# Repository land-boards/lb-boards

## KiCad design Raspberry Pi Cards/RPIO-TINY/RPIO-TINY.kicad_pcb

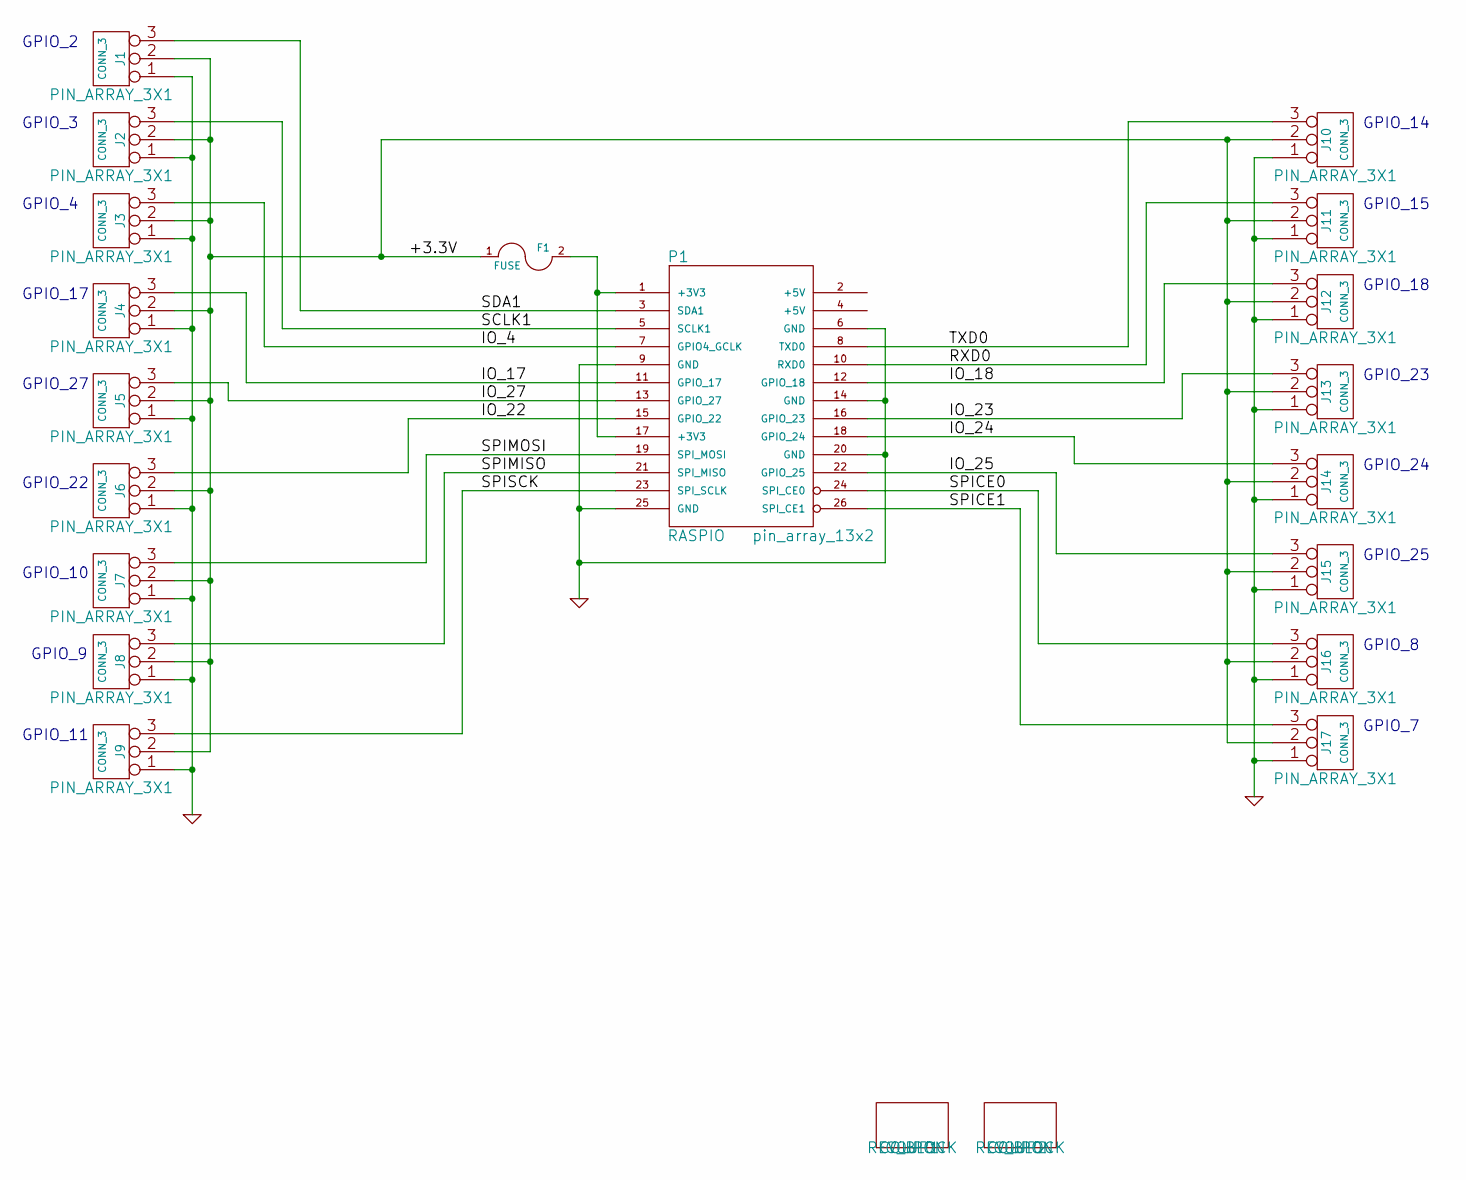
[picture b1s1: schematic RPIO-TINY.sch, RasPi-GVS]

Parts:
COUP1, COUP2: COUPON; REV_BLOCK
F1: FUSE
J1, J2, J3, J4, J5, J6, J7, J8, J9, J10, J11, J12, J13, J14, J15, J16, J17: CONN_3; PIN_ARRAY_3X1
P1: RASPIO; pin_array_13x2

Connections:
/+3.3V: F1.1, J1.2 (PM), J2.2 (PM), J3.2 (PM), J4.2 (PM), J5.2 (PM), J6.2 (PM), J7.2 (PM), J8.2 (PM), J9.2 (PM), J10.2 (PM), J11.2 (PM), J12.2 (PM), J13.2 (PM), J14.2 (PM), J15.2 (PM), J16.2 (PM), J17.2 (PM)
/IO_4: J3.3, P1.7 (GPIO4_GCLK)
/IO_17: J4.3, P1.11 (GPIO_17)
/IO_18: J12.3, P1.12 (GPIO_18)
/IO_22: J6.3, P1.15 (GPIO_22)
/IO_23: J13.3, P1.16 (GPIO_23)
/IO_24: J14.3, P1.18 (GPIO_24)
/IO_25: J15.3, P1.22 (GPIO_25)
/IO_27: J5.3, P1.13 (GPIO_27)
/RXD0: J11.3, P1.10 (RXD0)
/SCLK1: J2.3, P1.5 (SCLK1)
/SDA1: J1.3, P1.3 (SDA1)
/SPICE0: J16.3, P1.24 (SPI_CE0)
/SPICE1: J17.3, P1.26 (SPI_CE1)
/SPIMISO: J8.3, P1.21 (SPI_MISO)
/SPIMOSI: J7.3, P1.19 (SPI_MOSI)
/SPISCK: J9.3, P1.23 (SPI_SCLK)
/TXD0: J10.3, P1.8 (TXD0)
GND: J1.1, J2.1, J3.1, J4.1, J5.1, J6.1, J7.1, J8.1, J9.1, J10.1, J11.1, J12.1, J13.1, J14.1, J15.1, J16.1, J17.1, P1.6 (GND), P1.9 (GND), P1.14 (GND), P1.20 (GND), P1.25 (GND)
unnamed: F1.2, P1.1 (+3V3), P1.17 (+3V3)

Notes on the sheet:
GPIO_2
GPIO_3
GPIO_4
GPIO_17
GPIO_27
GPIO_22
GPIO_10
GPIO_9
GPIO_11
GPIO_14
GPIO_15
GPIO_18
GPIO_23
GPIO_24
GPIO_25
GPIO_8
GPIO_7

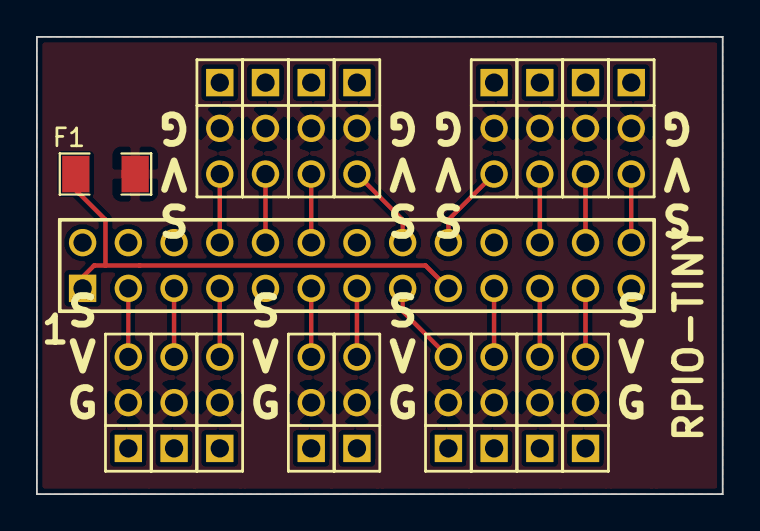
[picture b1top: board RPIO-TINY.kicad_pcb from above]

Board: 2 copper layers, 38.1 x 25.4 mm, 19 parts (0 on the bottom side), 20 nets.

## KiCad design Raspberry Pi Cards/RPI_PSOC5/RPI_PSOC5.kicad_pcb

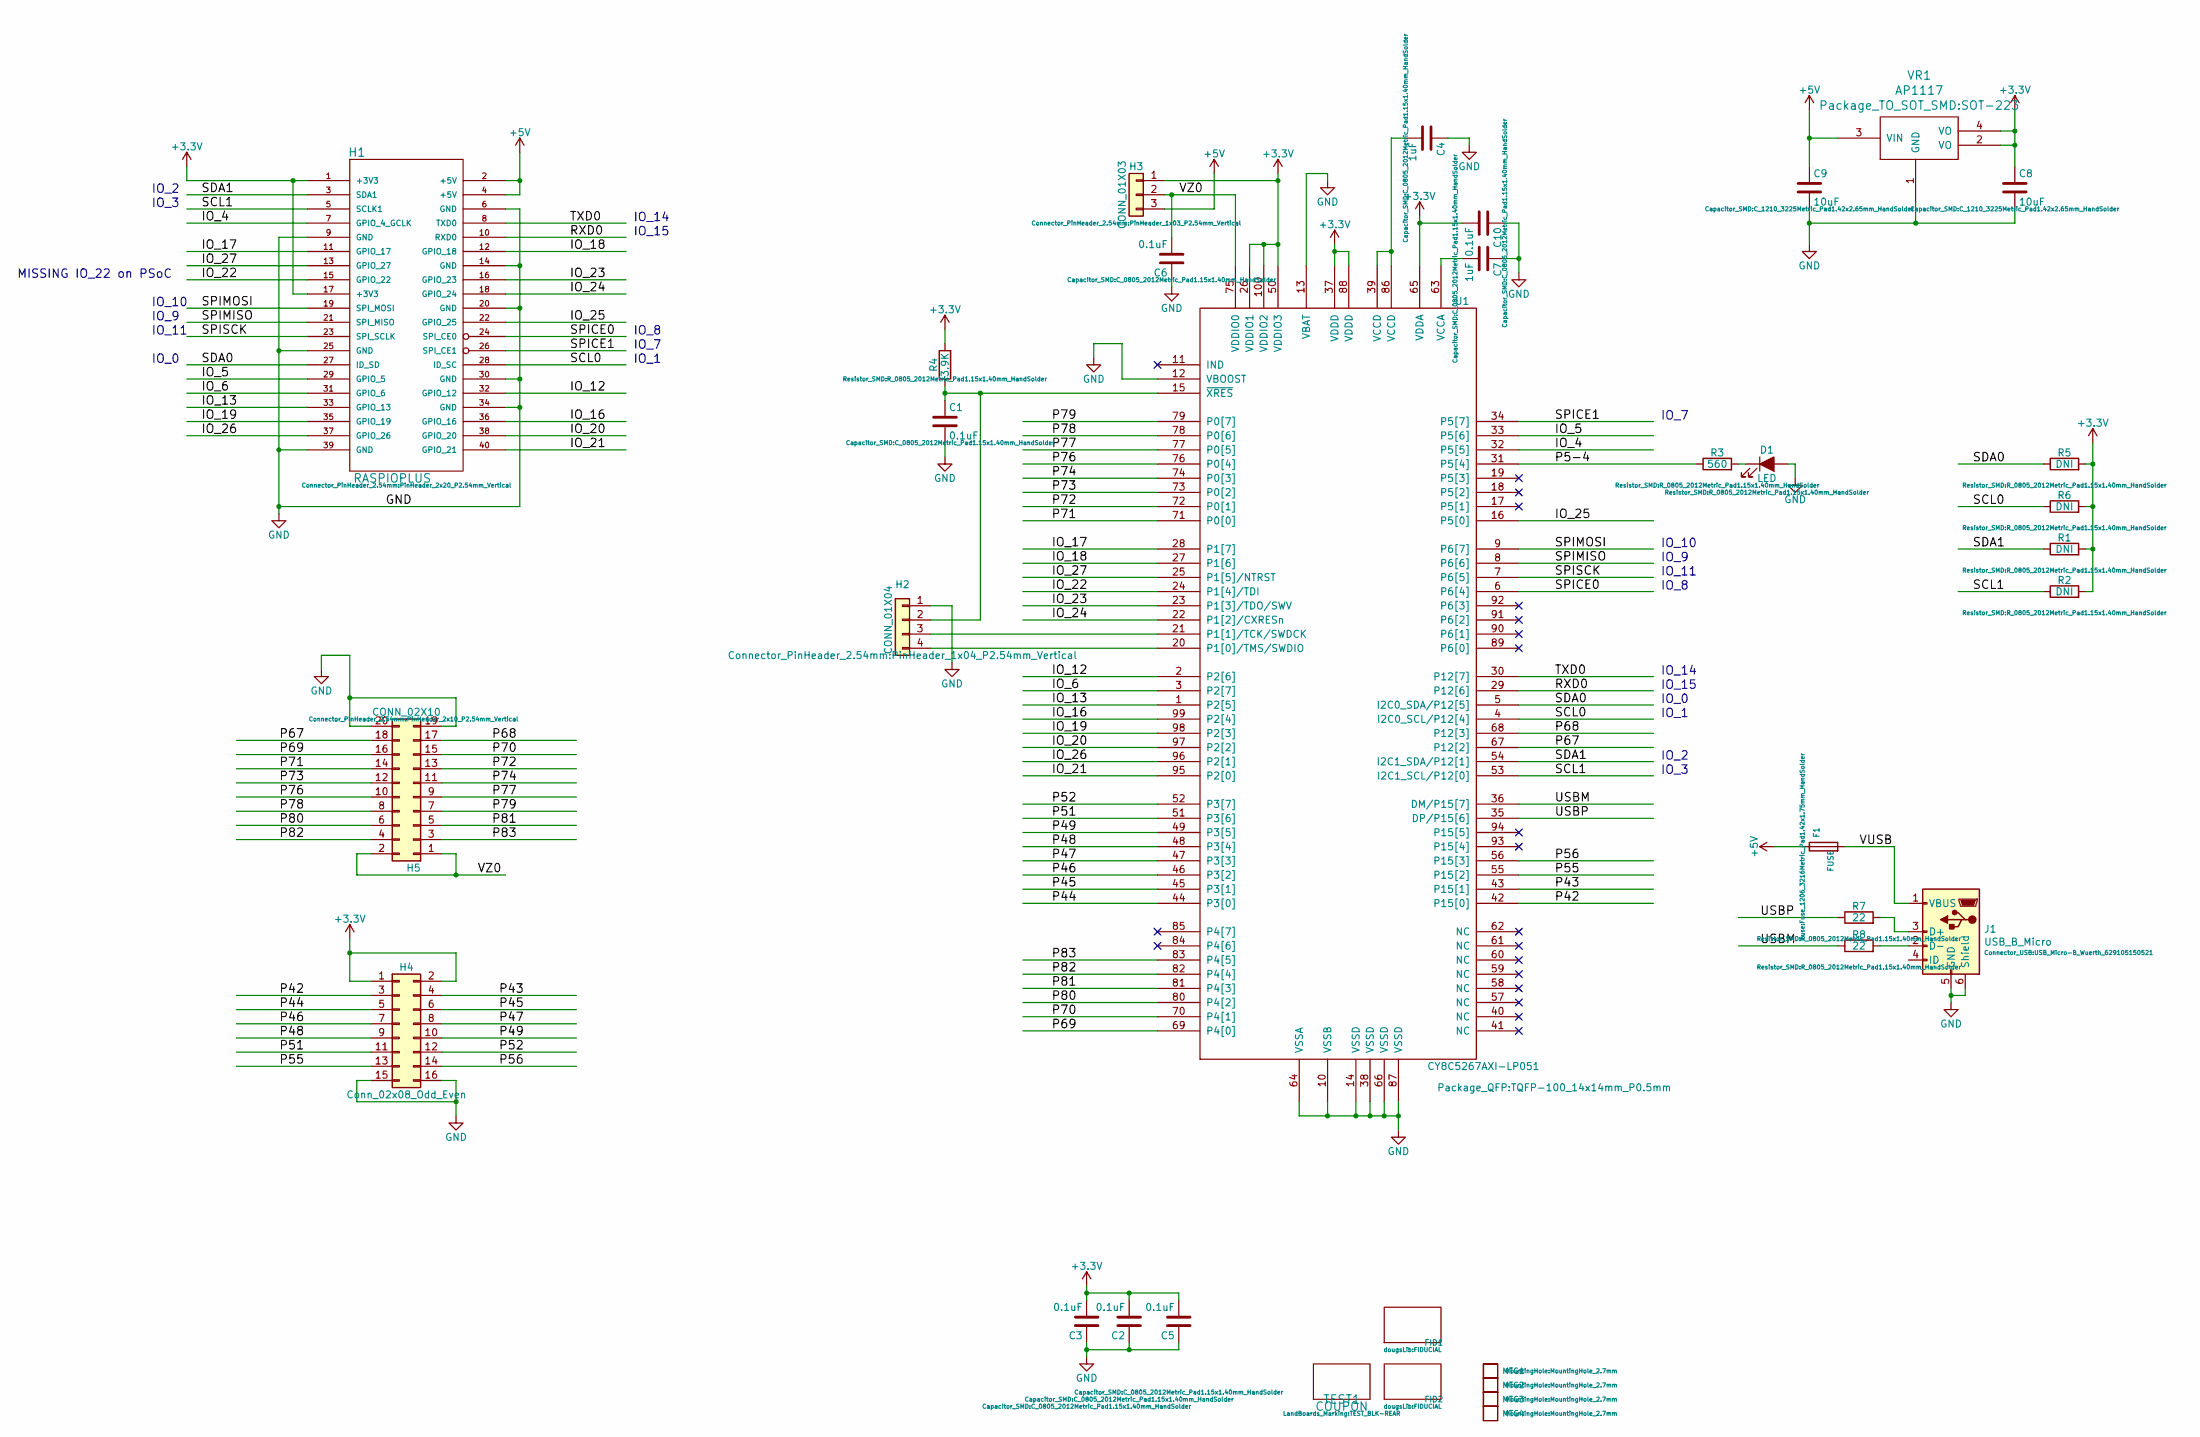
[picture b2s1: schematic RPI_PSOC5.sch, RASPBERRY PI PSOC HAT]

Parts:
C1, C2, C3, C5, C6, C10: 0.1uF; C_0805_2012Metric_Pad1.15x1.40mm_HandSolder
C4, C7: 1uF; C_0805_2012Metric_Pad1.15x1.40mm_HandSolder
C8, C9: 10uF; C_1210_3225Metric_Pad1.42x2.65mm_HandSolder
D1: LED; R_0805_2012Metric_Pad1.15x1.40mm_HandSolder
F1: FUSE; Fuse_1206_3216Metric_Pad1.42x1.75mm_HandSolder
FID1, FID2: CONN_1; FIDUCIAL
H1: RASPIOPLUS; PinHeader_2x20_P2.54mm_Vertical
H2: CONN_01X04; PinHeader_1x04_P2.54mm_Vertical
H3: CONN_01X03; PinHeader_1x03_P2.54mm_Vertical
H4: Conn_02x08_Odd_Even; PinHeader_2x08_P2.54mm_Vertical
H5: CONN_02X10; PinHeader_2x10_P2.54mm_Vertical
J1: USB_B_Micro; USB_Micro-B_Wuerth_629105150521
MTG1, MTG2, MTG3, MTG4: CONN_1; MountingHole_2.7mm
R1, R2, R5, R6: DNI; R_0805_2012Metric_Pad1.15x1.40mm_HandSolder
R3: 560; R_0805_2012Metric_Pad1.15x1.40mm_HandSolder
R4: 3.9K; R_0805_2012Metric_Pad1.15x1.40mm_HandSolder
R7, R8: 22; R_0805_2012Metric_Pad1.15x1.40mm_HandSolder
TEST1: COUPON; TEST_BLK-REAR
U1: CY8C5267AXI-LP051; TQFP-100_14x14mm_P0.5mm
VR1: AP1117; SOT-223

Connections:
+3V3: C2.2, C3.2, C5.2, C8.1, C10.2, H1.1 (+3V3), H1.17 (+3V3), H3.1, H4.1, H4.2, R1.2, R2.2, R4.2, R5.2, R6.2, U1.26 (VDDIO1), U1.37 (VDDD), U1.50 (VDDIO3), U1.65 (VDDA), U1.88 (VDDD), U1.100 (VDDIO2), VR1.2 (VO), VR1.4 (VO)
+5V: C9.1, F1.1, H1.2 (+5V), H1.4 (+5V), H3.3, VR1.3 (VIN)
/IO_4: H1.7 (GPIO_4_GCLK), U1.32 (P5[5])
/IO_5: H1.29 (GPIO_5), U1.33 (P5[6])
/IO_6: H1.31 (GPIO_6), U1.3 (P2[7])
/IO_12: H1.32 (GPIO_12), U1.2 (P2[6])
/IO_13: H1.33 (GPIO_13), U1.1 (P2[5])
/IO_16: H1.36 (GPIO_16), U1.99 (P2[4])
/IO_17: H1.11 (GPIO_17), U1.28 (P1[7])
/IO_18: H1.12 (GPIO_18), U1.27 (P1[6])
/IO_19: H1.35 (GPIO_19), U1.98 (P2[3])
/IO_20: H1.38 (GPIO_20), U1.97 (P2[2])
/IO_21: H1.40 (GPIO_21), U1.95 (P2[0])
/IO_22: H1.15 (GPIO_22), U1.24 (P1[4]/TDI)
/IO_23: H1.16 (GPIO_23), U1.23 (P1[3]/TDO/SWV)
/IO_24: H1.18 (GPIO_24), U1.22 (P1[2]/CXRESn)
/IO_25: H1.22 (GPIO_25), U1.16 (P5[0])
/IO_26: H1.37 (GPIO_26), U1.96 (P2[1])
/IO_27: H1.13 (GPIO_27), U1.25 (P1[5]/NTRST)
/P5-4: R3.1, U1.31 (P5[4])
/P42: H4.3, U1.42 (P15[0])
/P43: H4.4, U1.43 (P15[1])
/P44: H4.5, U1.44 (P3[0])
/P45: H4.6, U1.45 (P3[1])
/P46: H4.7, U1.46 (P3[2])
/P47: H4.8, U1.47 (P3[3])
/P48: H4.9, U1.48 (P3[4])
/P49: H4.10, U1.49 (P3[5])
/P51: H4.11, U1.51 (P3[6])
/P52: H4.12, U1.52 (P3[7])
/P55: H4.13, U1.55 (P15[2])
/P56: H4.14, U1.56 (P15[3])
/P67: H5.18, U1.67 (P12[2])
/P68: H5.17, U1.68 (P12[3])
/P69: H5.16, U1.69 (P4[0])
/P70: H5.15, U1.70 (P4[1])
/P71: H5.14, U1.71 (P0[0])
/P72: H5.13, U1.72 (P0[1])
/P73: H5.12, U1.73 (P0[2])
/P74: H5.11, U1.74 (P0[3])
/P76: H5.10, U1.76 (P0[4])
/P77: H5.9, U1.77 (P0[5])
/P78: H5.8, U1.78 (P0[6])
/P79: H5.7, U1.79 (P0[7])
/P80: H5.6, U1.80 (P4[2])
/P81: H5.5, U1.81 (P4[3])
/P82: H5.4, U1.82 (P4[4])
/P83: H5.3, U1.83 (P4[5])
/RXD0: H1.10 (RXD0), U1.29 (P12[6])
/SCL0: H1.28 (ID_SC), R6.1, U1.4 (I2C0_SCL/P12[4])
/SCL1: H1.5 (SCLK1), R2.1, U1.53 (I2C1_SCL/P12[0])
/SDA0: H1.27 (ID_SD), R5.1, U1.5 (I2C0_SDA/P12[5])
/SDA1: H1.3 (SDA1), R1.1, U1.54 (I2C1_SDA/P12[1])
/SPICE0: H1.24 (SPI_CE0), U1.6 (P6[4])
/SPICE1: H1.26 (SPI_CE1), U1.34 (P5[7])
/SPIMISO: H1.21 (SPI_MISO), U1.8 (P6[6])
/SPIMOSI: H1.19 (SPI_MOSI), U1.9 (P6[7])
/SPISCK: H1.23 (SPI_SCLK), U1.7 (P6[5])
/TXD0: H1.8 (TXD0), U1.30 (P12[7])
/USBM: R8.1, U1.36 (DM/P15[7])
/USBP: R7.1, U1.35 (DP/P15[6])
/VUSB: F1.2, J1.1 (VBUS)
/VZ0: C6.2, H3.2, H5.1, H5.2, U1.75 (VDDIO0)
GND: C1.2, C2.1, C3.1, C4.1, C5.1, C6.1, C7.1, C8.2, C9.2, C10.1, D1.2 (A), H1.6 (GND), H1.9 (GND), H1.14 (GND), H1.20 (GND), H1.25 (GND), H1.30 (GND), H1.34 (GND), H1.39 (GND), H2.1, H4.15, H4.16, H5.19, H5.20, J1.5 (GND), J1.6 (Shield), U1.10 (VSSB), U1.12 (VBOOST), U1.13 (VBAT), U1.14 (VSSD), U1.38 (VSSD), U1.64 (VSSA), U1.66 (VSSD), U1.87 (VSSD), VR1.1 (GND)
unnamed: C1.1, H2.2, R4.1, U1.15 (~XRES)
unnamed: C4.2, U1.39 (VCCD), U1.86 (VCCD)
unnamed: C7.2, U1.63 (VCCA)
unnamed: D1.1 (K), R3.2
unnamed: H2.3, U1.21 (P1[1]/TCK/SWDCK)
unnamed: H2.4, U1.20 (P1[0]/TMS/SWDIO)
unnamed: J1.2 (D-), R8.2
unnamed: J1.3 (D+), R7.2

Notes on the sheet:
MISSING IO_22 on PSoC
IO_2
IO_3
IO_10
IO_9
IO_11
IO_14
IO_15
IO_8
IO_7
IO_1
IO_0

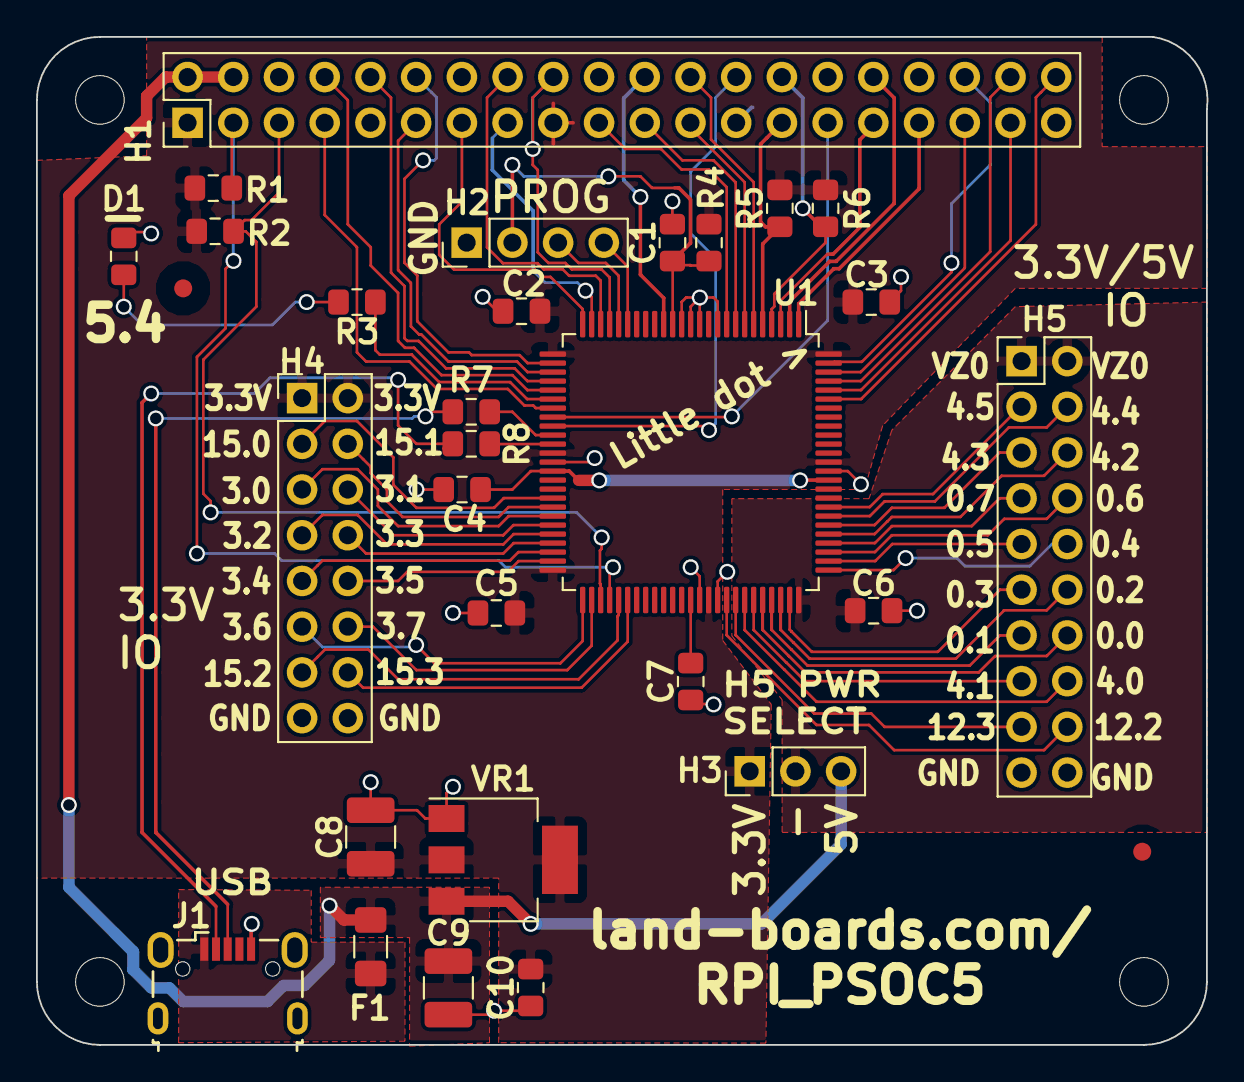
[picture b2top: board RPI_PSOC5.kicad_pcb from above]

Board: 2 copper layers, 65.0 x 56.0 mm, 35 parts (0 on the bottom side), 72 nets.

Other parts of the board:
TEST: COUPON; TEST_BLK-REAR

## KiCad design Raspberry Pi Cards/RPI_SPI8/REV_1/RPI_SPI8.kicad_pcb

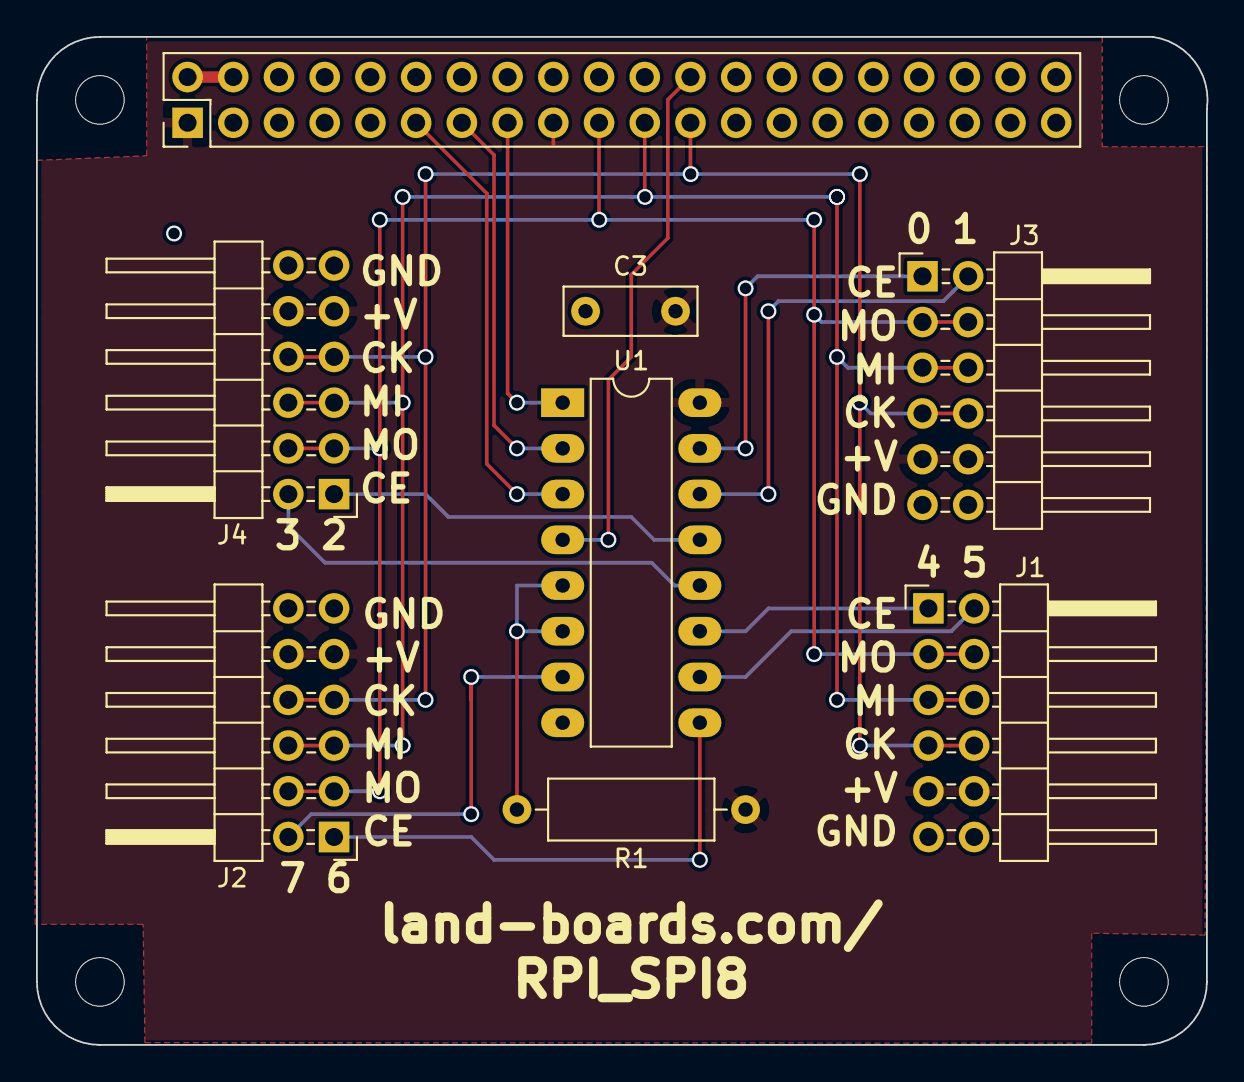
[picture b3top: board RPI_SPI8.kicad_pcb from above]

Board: 2 copper layers, 65.0 x 56.0 mm, 13 parts (0 on the bottom side), 19 nets.

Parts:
C3: 0.1uF; C_Rect_L7.2mm_W2.5mm_P5.00mm_FKS2_FKP2_MKS2_MKP2
H1: RASPIOPLUS; PinHeader_2x20_P2.54mm_Vertical
J1, J2, J3, J4: Conn_02x06_Odd_Even; PinHeader_2x06_P2.54mm_Horizontal
MTG1, MTG2, MTG3, MTG4: CONN_1; MountingHole_2.7mm
R1: 10K; R_Axial_DIN0309_L9.0mm_D3.2mm_P12.70mm_Horizontal
TEST: COUPON; TEST_BLK-REAR
U1: 74LS138; DIP-16_W7.62mm_LongPads

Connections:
+3V3: C3.2, H1.1, H1.17, J1.9, J1.10, J2.9, J2.10, J3.9, J3.10, J4.9, J4.10, R1.1, U1.16
+5V: H1.2, H1.4
/IO_17: H1.11, U1.3
/IO_22: H1.15, U1.1
/IO_27: H1.13, U1.2
/SPICE0: H1.24, U1.4
/SPICE0A: J3.1, U1.15
/SPICE0B: J3.2, U1.14
/SPICE0C: J4.1, U1.13
/SPICE0D: J4.2, U1.12
/SPICE0E: J1.1, U1.11
/SPICE0F: J1.2, U1.10
/SPICE0G: J2.1, U1.9
/SPICE0H: J2.2, U1.7
/SPIMISO: H1.21, J1.5, J1.6, J2.5, J2.6, J3.5, J3.6, J4.5, J4.6
/SPIMOSI: H1.19, J1.3, J1.4, J2.3, J2.4, J3.3, J3.4, J4.3, J4.4
/SPISCK: H1.23, J1.7, J1.8, J2.7, J2.8, J3.7, J3.8, J4.7, J4.8
GND: C3.1, H1.6, H1.9, H1.14, H1.20, H1.25, H1.30, H1.34, H1.39, J1.11, J1.12, J2.11, J2.12, J3.11, J3.12, J4.11, J4.12, U1.8
unnamed: R1.2, U1.5, U1.6

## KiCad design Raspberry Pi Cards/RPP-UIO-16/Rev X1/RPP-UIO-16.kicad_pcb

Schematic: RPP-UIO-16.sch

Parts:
C1, C2, C3, C4, C5: 0.1uF; SM0805
COUP?1, COUP?2: COUPON; REV_BLOCK
F1, F2: FUSE; SM1206
FID1, FID2: CONN_1; FIDUCIAL
J1, J2: CONN_4; PIN_ARRAY_4x1
J3, J4, J5, J6, J7, J8, J9, J12, J13, J14, J15, J16, J17, J18, J19, J20, J21, J25, J26, J27, J28, J29, J30, J31, J32, J34, J35, J36, J37, J38, J39, J40, J41: CONN_3; PIN_ARRAY_3X1
J10, J11: CONN_6; PIN_ARRAY-6X1
J22: CONN_2; PIN_ARRAY_2X1
J23, J33: CONN_8; PIN_ARRAY-8X1
J24: RASPIOPLUS; PIN_ARRAY_20X2
MTG1, MTG2, MTG3, MTG4: CONN_1; MTG-2.75MM
P1: CONN_2; TB2-5MM
P2: CONN_2; PIN_ARRAY_2X1
R1, R2: 3.9K; SM0805
R3: 1K; SM0805
U1: 24C512; SO8E-wider
U2, U3: TXB0108; SOG20

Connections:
/+3.3V: C1.1, C2.1, C4.1, F2.2, J1.2, J2.2, J3.2 (PM), J4.2 (PM), J5.2 (PM), J6.2 (PM), J7.2 (PM), J8.2 (PM), J9.2 (PM), J10.2, J11.2, J12.2 (PM), J13.2 (PM), J14.2 (PM), J15.2 (PM), J16.2 (PM), J17.2 (PM), J18.2 (PM), J19.2 (PM), J20.2 (PM), J21.2 (PM), R1.1, R2.1, R3.1, U1.8 (VCC), U2.2 (VCCA(LV)), U2.10 (OE), U3.2 (VCCA(LV)), U3.10 (OE)
/+5V: C3.1, C5.1, J25.2 (PM), J26.2 (PM), J27.2 (PM), J28.2 (PM), J29.2 (PM), J30.2 (PM), J31.2 (PM), J32.2 (PM), J34.2 (PM), J35.2 (PM), J36.2 (PM), J37.2 (PM), J38.2 (PM), J39.2 (PM), J40.2 (PM), J41.2 (PM), P1.2 (PM), P2.1, U2.19 (VCCB(HV)), U3.19 (VCCB(HV))
/IO_4: J21.3, J24.7 (GPIO4_GCLK)
/IO_5: J12.3, J24.29 (GPIO5)
/IO_6: J13.3, J24.31 (GPIO_6)
/IO_12: J18.3, J24.32 (GPIO_12)
/IO_13: J14.3, J24.33 (GPIO_13)
/IO_16: J19.3, J24.36 (GPIO_16)
/IO_17: J4.3, J24.11 (GPIO_17)
/IO_18: J3.3, J24.12 (GPIO_18)
/IO_19: J15.3, J24.35 (GPIO_19)
/IO_20: J20.3, J24.38 (GPIO_20)
/IO_21: J17.3, J24.40 (GPIO_21)
/IO_22: J7.3, J24.15 (GPIO_22)
/IO_23: J6.3, J24.16 (GPIO_23)
/IO_24: J8.3, J24.18 (GPIO_24)
/IO_25: J9.3, J24.22 (GPIO_25)
/IO_26: J16.3, J24.37 (GPIO_26)
/IO_27: J5.3, J24.13 (GPIO_27)
/RXD0: J2.4, J24.10 (RXD0)
/SCL: J24.28 (ID_SC), R2.2, U1.6 (SCL)
/SCLK1: J1.4, J24.5 (SCLK1)
/SDA: J24.27 (ID_SD), R1.2, U1.5 (SDA)
/SDA1: J1.3, J24.3 (SDA1)
/SPICE0: J10.6, J24.24 (SPI_CE0)
/SPICE1: J11.6, J24.26 (SPI_CE1)
/SPIMISO: J10.4, J11.4, J24.21 (SPI_MISO)
/SPIMOSI: J10.3, J11.3, J24.19 (SPI_MOSI)
/SPISCK: J10.5, J11.5, J24.23 (SPI_SCLK)
/TXD0: J2.3, J24.8 (TXD0)
/WR: J22.1, R3.2, U1.7 (TEST)
unnamed: F1.1, J24.2 (+5V), J24.4 (+5V)
unnamed: J23.8, U2.1 (A1)
unnamed: J23.7, U2.3 (A2)
unnamed: J23.6, U2.4 (A3)
unnamed: J23.5, U2.5 (A4)
unnamed: J23.4, U2.6 (A5)
unnamed: J23.3, U2.7 (A6)
unnamed: J23.2, U2.8 (A7)
unnamed: J23.1, U2.9 (A8)
unnamed: J25.3, U2.20 (B1)
unnamed: J28.3, U2.16 (B4)
unnamed: J27.3, U2.17 (B3)
unnamed: J26.3, U2.18 (G2)
unnamed: J32.3, U2.12 (B8)
unnamed: J31.3, U2.13 (B7)
unnamed: J30.3, U2.14 (B6)
unnamed: J29.3, U2.15 (B5)
unnamed: J33.1, U3.9 (A8)
unnamed: J33.8, U3.1 (A1)
unnamed: J33.7, U3.3 (A2)
unnamed: J33.6, U3.4 (A3)
unnamed: J33.5, U3.5 (A4)
unnamed: J33.4, U3.6 (A5)
unnamed: J33.3, U3.7 (A6)
unnamed: J33.2, U3.8 (A7)
unnamed: J35.3, U3.18 (G2)
unnamed: J34.3, U3.20 (B1)
unnamed: F1.2, P2.2 (PM)
unnamed: J41.3, U3.12 (B8)
unnamed: J40.3, U3.13 (B7)
unnamed: J39.3, U3.14 (B6)
unnamed: J38.3, U3.15 (B5)
unnamed: J37.3, U3.16 (B4)
unnamed: J36.3, U3.17 (B3)
unnamed: F2.1, J24.1 (+3V3), J24.17 (+3V3)

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
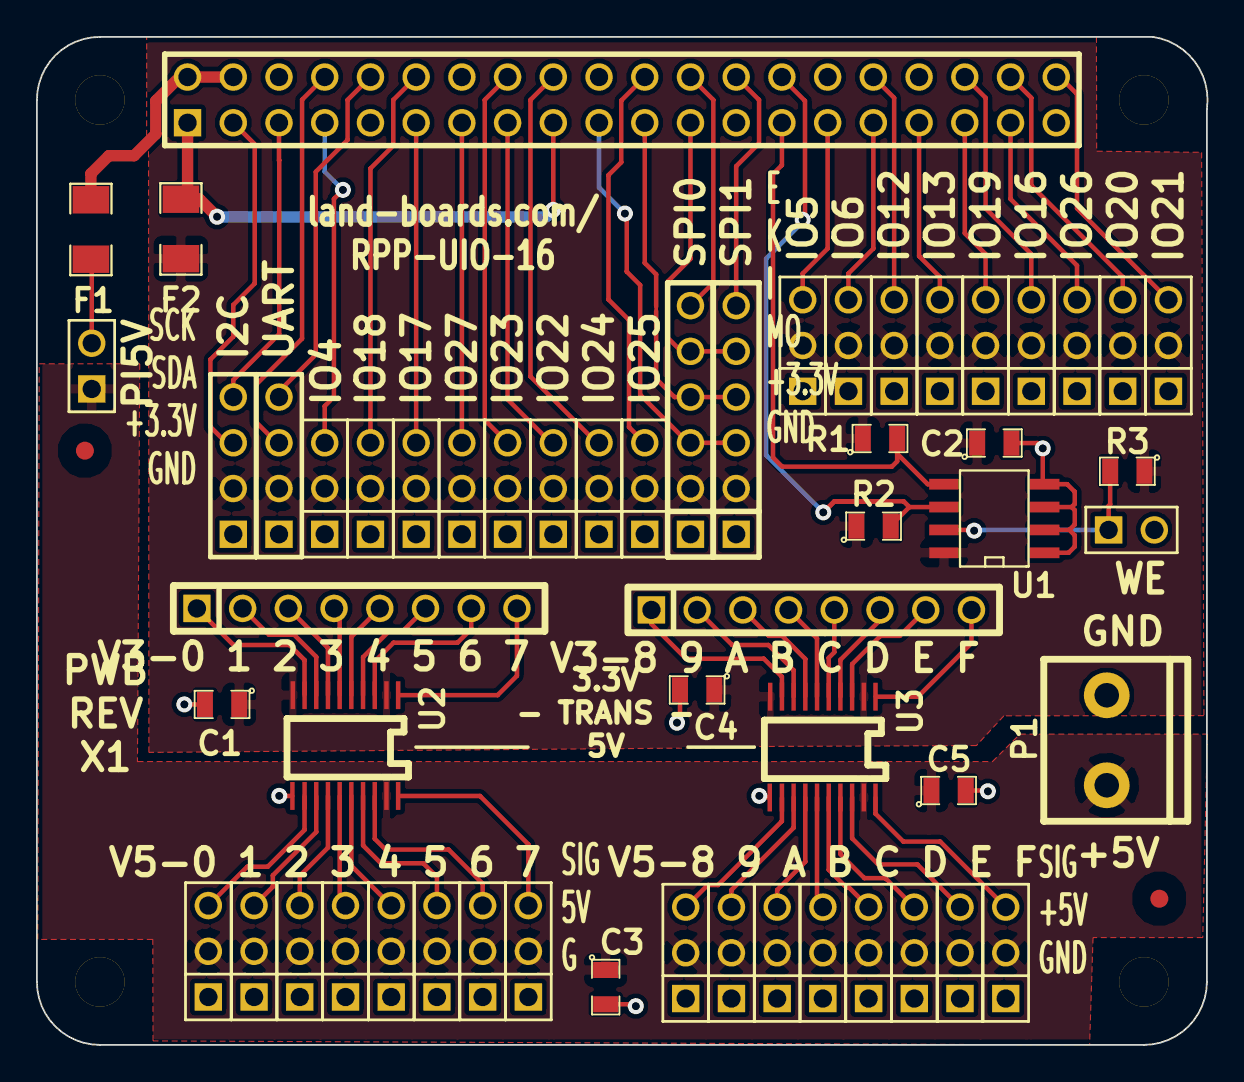
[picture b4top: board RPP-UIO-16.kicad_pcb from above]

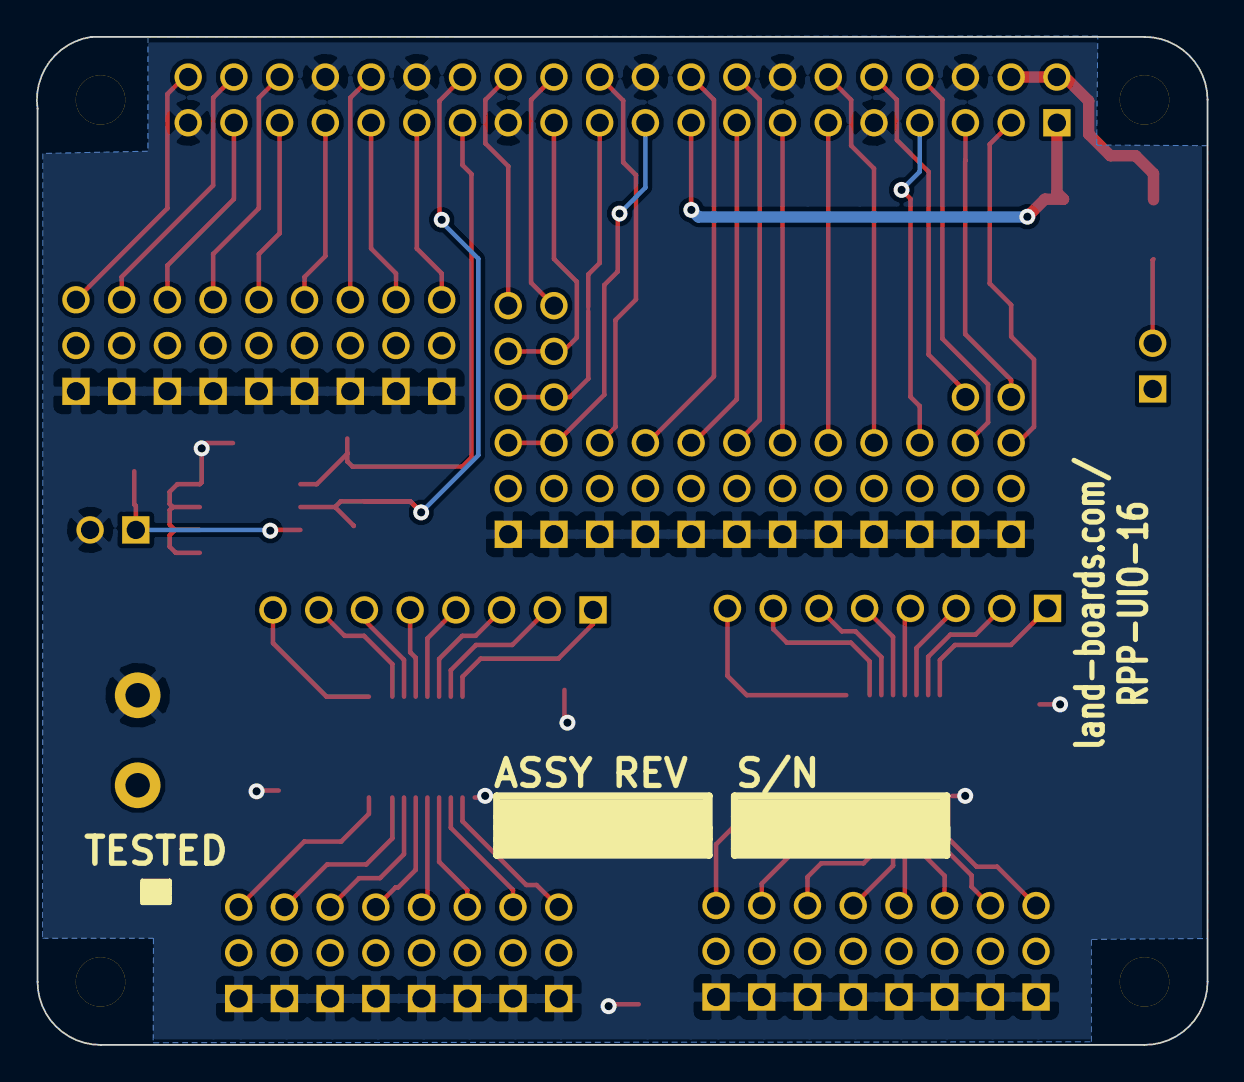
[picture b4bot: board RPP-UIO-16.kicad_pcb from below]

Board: 2 copper layers, 65.0 x 56.0 mm, 64 parts (2 on the bottom side), 67 nets.

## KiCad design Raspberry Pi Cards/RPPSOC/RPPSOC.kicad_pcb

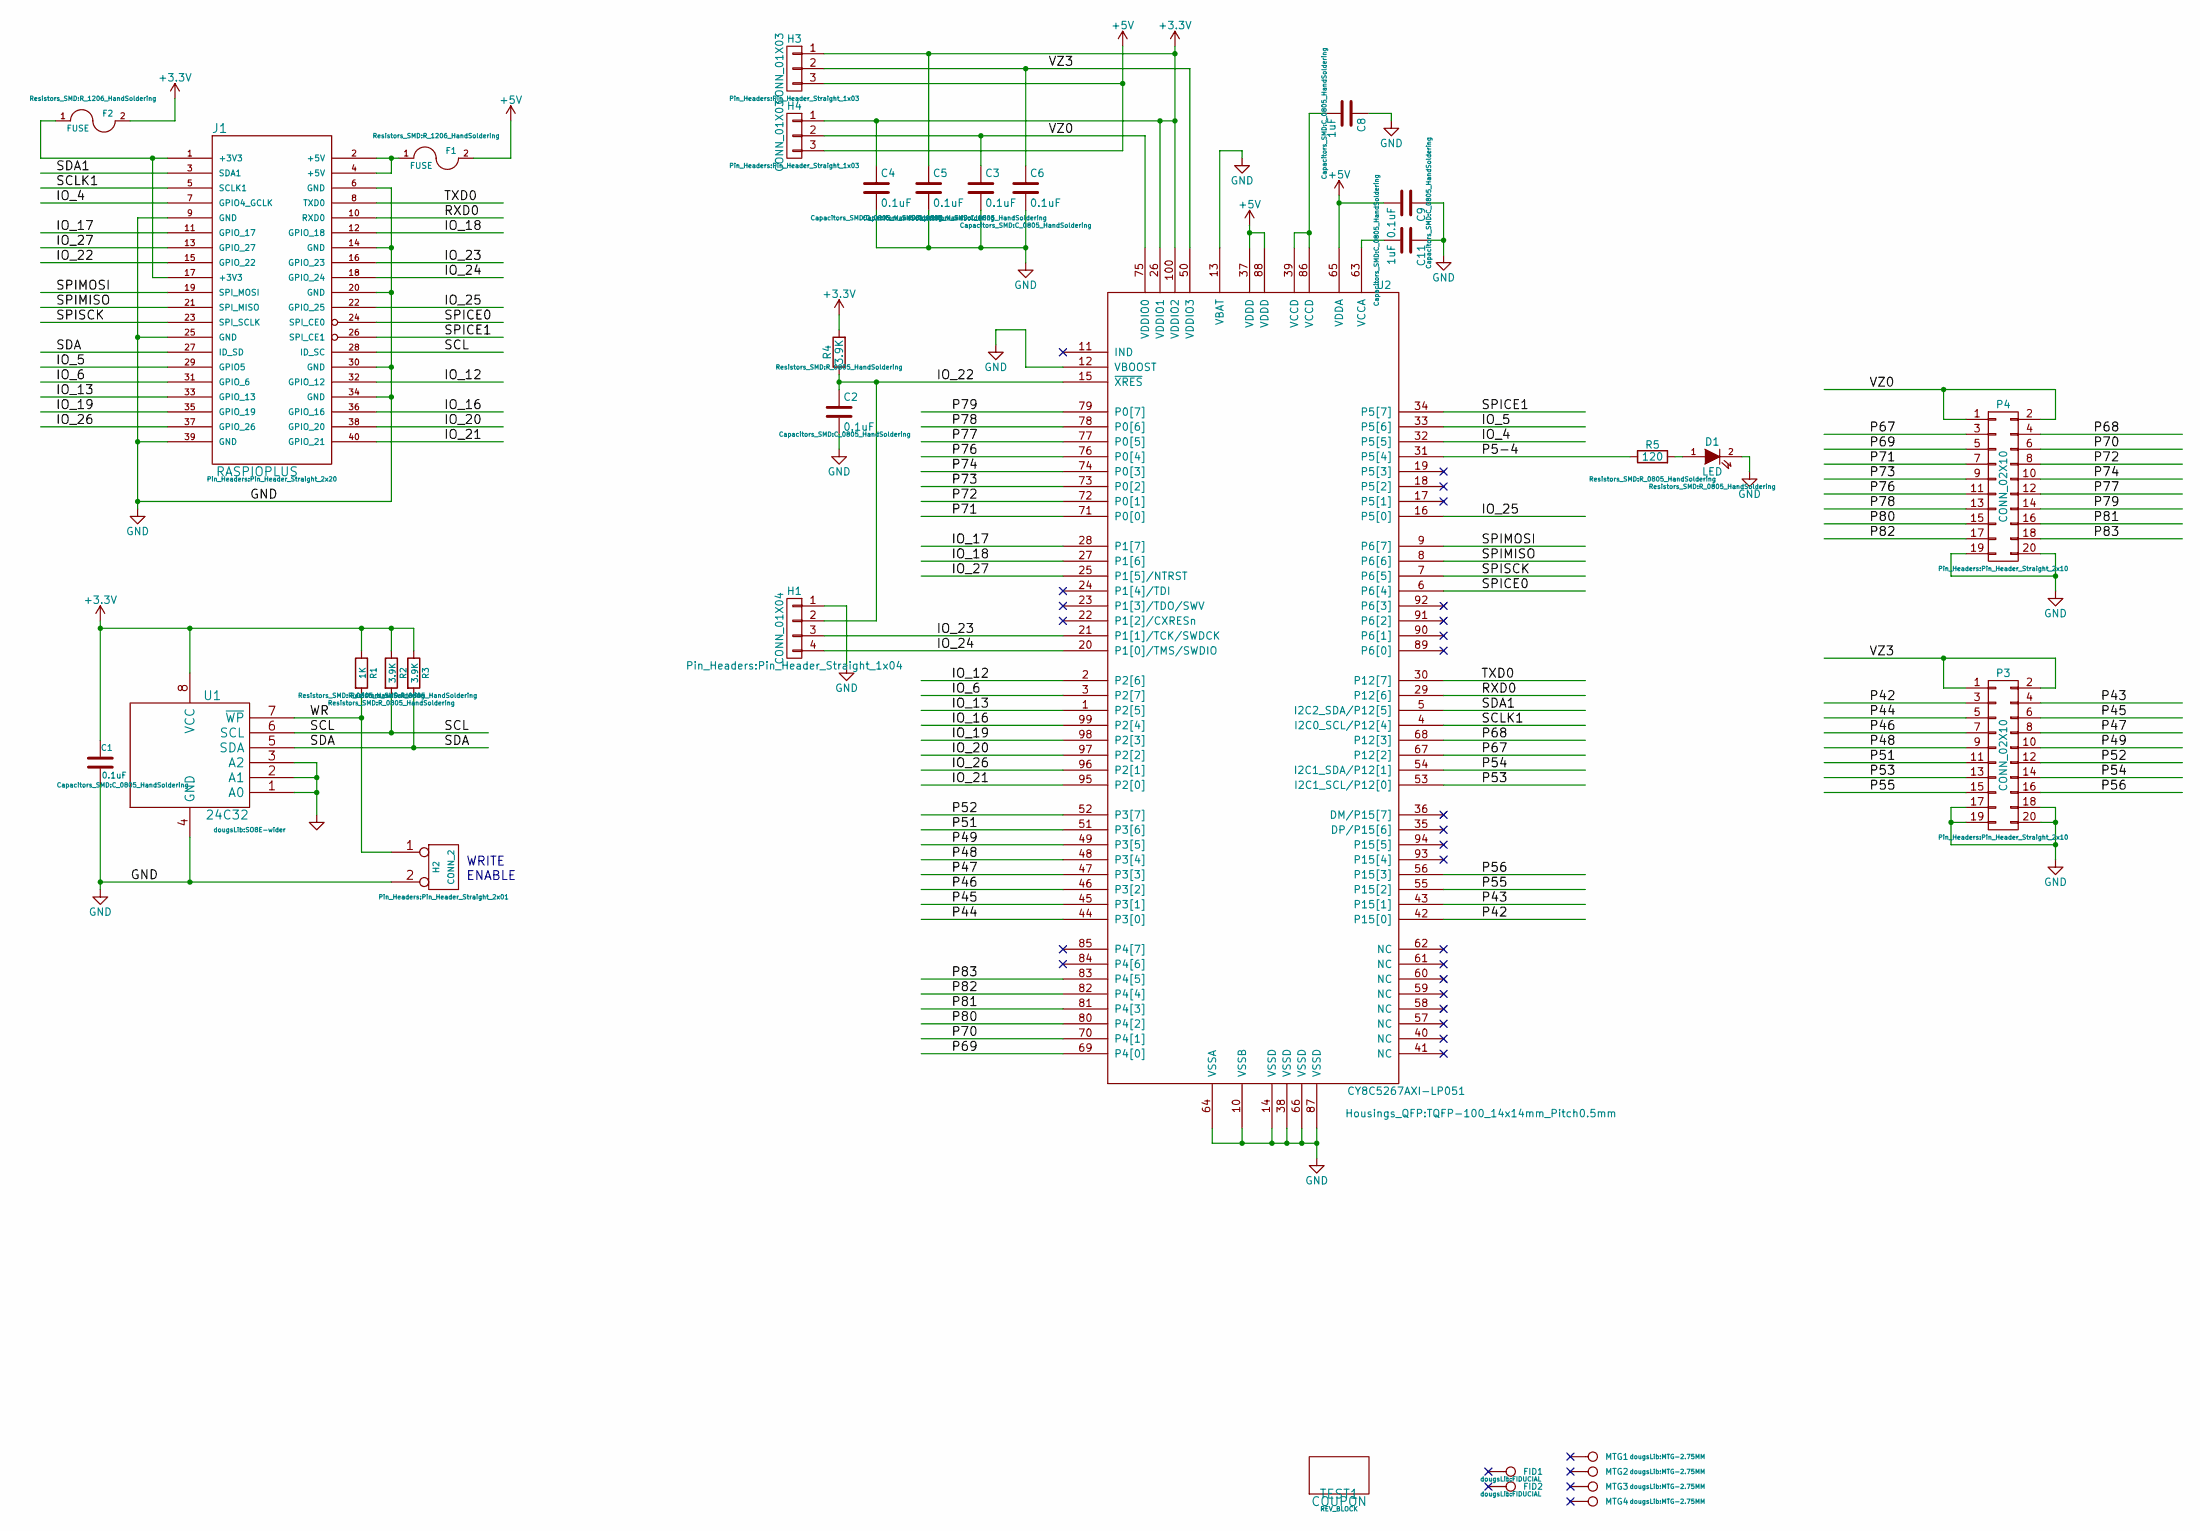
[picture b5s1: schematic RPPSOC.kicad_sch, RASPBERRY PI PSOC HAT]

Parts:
C1, C2, C3, C4, C5, C6, C9: 0.1uF; C_0805_HandSoldering
C8, C11: 1uF; C_0805_HandSoldering
D1: LED; R_0805_HandSoldering
F1, F2: FUSE; R_1206_HandSoldering
FID1, FID2: CONN_1; FIDUCIAL
H1: CONN_01X04; Pin_Header_Straight_1x04
H2: CONN_2; Pin_Header_Straight_2x01
H3, H4: CONN_01X03; Pin_Header_Straight_1x03
J1: RASPIOPLUS; Pin_Header_Straight_2x20
MTG1, MTG2, MTG3, MTG4: CONN_1; MTG-2.75MM
P3, P4: CONN_02X10; Pin_Header_Straight_2x10
R1: 1K; R_0805_HandSoldering
R2, R3, R4: 3.9K; R_0805_HandSoldering
R5: 120; R_0805_HandSoldering
TEST1: COUPON; REV_BLOCK
U1: 24C32; SO8E-wider
U2: CY8C5267AXI-LP051; TQFP-100_14x14mm_Pitch0.5mm

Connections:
+3V3: C1.1, C4.1, C5.1, F2.2, H3.1, H4.1, R1.1, R2.1, R3.1, R4.2, U1.8 (VCC), U2.26 (VDDIO1), U2.100 (VDDIO2)
+5V: C9.2, F1.2, H3.3, H4.3, U2.37 (VDDD), U2.65 (VDDA), U2.88 (VDDD)
/IO_4: J1.7 (GPIO4_GCLK), U2.32 (P5[5])
/IO_5: J1.29 (GPIO5), U2.33 (P5[6])
/IO_6: J1.31 (GPIO_6), U2.3 (P2[7])
/IO_12: J1.32 (GPIO_12), U2.2 (P2[6])
/IO_13: J1.33 (GPIO_13), U2.1 (P2[5])
/IO_16: J1.36 (GPIO_16), U2.99 (P2[4])
/IO_17: J1.11 (GPIO_17), U2.28 (P1[7])
/IO_18: J1.12 (GPIO_18), U2.27 (P1[6])
/IO_19: J1.35 (GPIO_19), U2.98 (P2[3])
/IO_20: J1.38 (GPIO_20), U2.97 (P2[2])
/IO_21: J1.40 (GPIO_21), U2.95 (P2[0])
/IO_22: C2.1, H1.2, J1.15 (GPIO_22), R4.1, U2.15 (~XRES)
/IO_23: H1.3, J1.16 (GPIO_23), U2.21 (P1[1]/TCK/SWDCK)
/IO_24: H1.4, J1.18 (GPIO_24), U2.20 (P1[0]/TMS/SWDIO)
/IO_25: J1.22 (GPIO_25), U2.16 (P5[0])
/IO_26: J1.37 (GPIO_26), U2.96 (P2[1])
/IO_27: J1.13 (GPIO_27), U2.25 (P1[5]/NTRST)
/P5-4: R5.1, U2.31 (P5[4])
/P42: P3.3, U2.42 (P15[0])
/P43: P3.4, U2.43 (P15[1])
/P44: P3.5, U2.44 (P3[0])
/P45: P3.6, U2.45 (P3[1])
/P46: P3.7, U2.46 (P3[2])
/P47: P3.8, U2.47 (P3[3])
/P48: P3.9, U2.48 (P3[4])
/P49: P3.10, U2.49 (P3[5])
/P51: P3.11, U2.51 (P3[6])
/P52: P3.12, U2.52 (P3[7])
/P53: P3.13, U2.53 (I2C1_SCL/P12[0])
/P54: P3.14, U2.54 (I2C1_SDA/P12[1])
/P55: P3.15, U2.55 (P15[2])
/P56: P3.16, U2.56 (P15[3])
/P67: P4.3, U2.67 (P12[2])
/P68: P4.4, U2.68 (P12[3])
/P69: P4.5, U2.69 (P4[0])
/P70: P4.6, U2.70 (P4[1])
/P71: P4.7, U2.71 (P0[0])
/P72: P4.8, U2.72 (P0[1])
/P73: P4.9, U2.73 (P0[2])
/P74: P4.10, U2.74 (P0[3])
/P76: P4.11, U2.76 (P0[4])
/P77: P4.12, U2.77 (P0[5])
/P78: P4.13, U2.78 (P0[6])
/P79: P4.14, U2.79 (P0[7])
/P80: P4.15, U2.80 (P4[2])
/P81: P4.16, U2.81 (P4[3])
/P82: P4.17, U2.82 (P4[4])
/P83: P4.18, U2.83 (P4[5])
/RXD0: J1.10 (RXD0), U2.29 (P12[6])
/SCL: J1.28 (ID_SC), R2.2, U1.6 (SCL)
/SCLK1: J1.5 (SCLK1), U2.4 (I2C0_SCL/P12[4])
/SDA: J1.27 (ID_SD), R3.2, U1.5 (SDA)
/SDA1: J1.3 (SDA1), U2.5 (I2C2_SDA/P12[5])
/SPICE0: J1.24 (SPI_CE0), U2.6 (P6[4])
/SPICE1: J1.26 (SPI_CE1), U2.34 (P5[7])
/SPIMISO: J1.21 (SPI_MISO), U2.8 (P6[6])
/SPIMOSI: J1.19 (SPI_MOSI), U2.9 (P6[7])
/SPISCK: J1.23 (SPI_SCLK), U2.7 (P6[5])
/TXD0: J1.8 (TXD0), U2.30 (P12[7])
/VZ0: C3.1, H4.2, P4.1, P4.2, U2.75 (VDDIO0); also elsewhere on the board
/VZ3: C6.1, H3.2, P3.1, P3.2, U2.50 (VDDIO3)
/WR: H2.1, R1.2, U1.7 (~WP)
GND: C1.2, C2.2, C3.2, C4.2, C5.2, C6.2, C8.1, C9.1, C11.1, D1.2 (K), H1.1, H2.2 (PM), J1.6 (GND), J1.9 (GND), J1.14 (GND), J1.20 (GND), J1.25 (GND), J1.30 (GND), J1.34 (GND), J1.39 (GND), P3.17, P3.18, P3.19, P3.20, P4.19, P4.20, U1.1 (A0), U1.2 (A1), U1.3 (A2), U1.4 (GND), U2.10 (VSSB), U2.12 (VBOOST), U2.13 (VBAT), U2.14 (VSSD), U2.38 (VSSD), U2.64 (VSSA), U2.66 (VSSD), U2.87 (VSSD); also elsewhere on the board
unnamed: C8.2, U2.39 (VCCD), U2.86 (VCCD)
unnamed: C11.2, U2.63 (VCCA)
unnamed: D1.1 (A), R5.2
unnamed: F1.1, J1.2 (+5V), J1.4 (+5V)
unnamed: F2.1, J1.1 (+3V3), J1.17 (+3V3)

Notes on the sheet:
WRITE ENABLE
